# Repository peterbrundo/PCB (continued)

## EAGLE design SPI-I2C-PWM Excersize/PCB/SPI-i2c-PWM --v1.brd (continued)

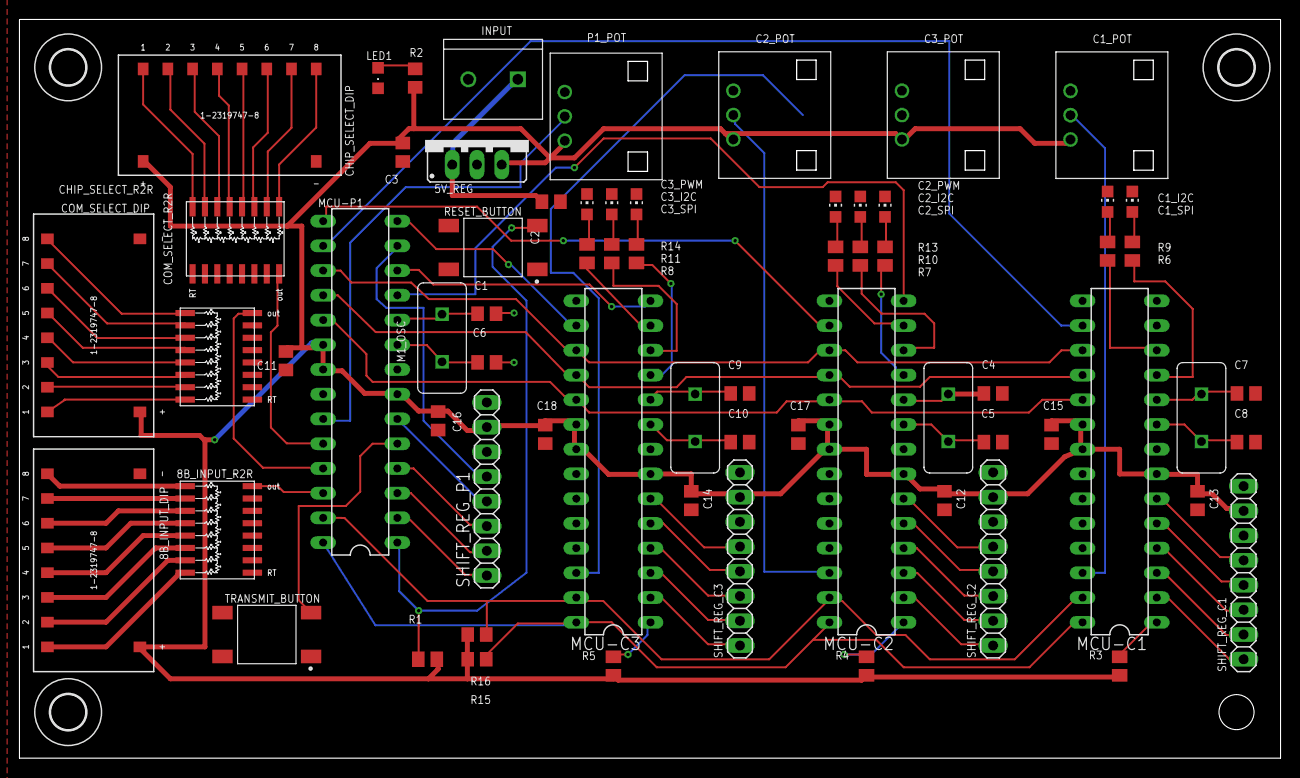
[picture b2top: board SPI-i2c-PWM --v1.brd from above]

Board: 2 copper layers, 129.4 x 75.7 mm, 72 parts (1 on the bottom side), 90 nets.

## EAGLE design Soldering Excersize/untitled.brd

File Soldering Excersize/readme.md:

# Soldering Practice
## Purpose
- First ever PCB (outside of work)
- Use spare parts on hand
  - Use NPN transistor
  - Use optoisolator
  - Voltage divider
- Different voltages +3.3V , +5V
- Surface mount soldering
  - 0805 Led & Resistor circuits
- Soldering practice

## Thoughts and reflections
- Good soldering practice
- Hard to re-use the board for other projects
  - next time include mounting holes
  - better breakouts for pin headers (hook up connections)
- [x] Never look back

*edit 11/29/2021*

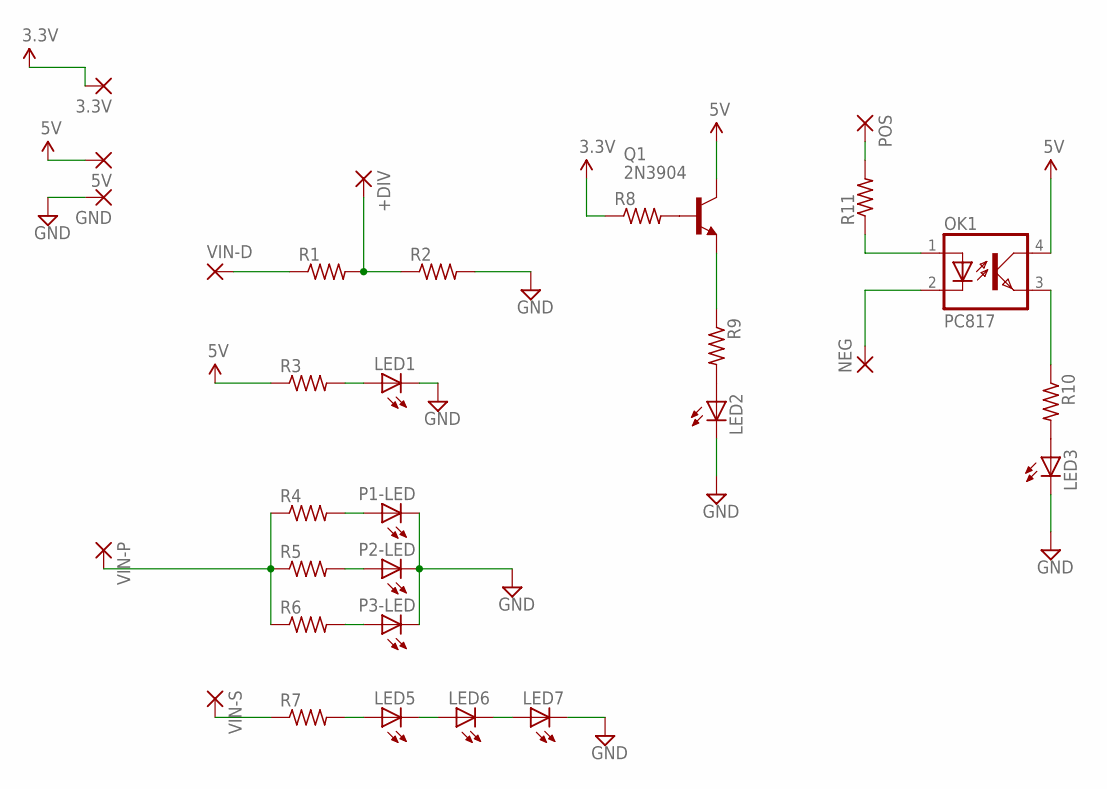
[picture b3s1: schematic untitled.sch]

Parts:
3.3V, 5V: 2,54/1,0
+DIV: 2,54/1,0
GND: 2,54/1,0
LED1, LED2, LED3, LED5, LED6, LED7: LEDCHIPLED_0805; CHIPLED_0805
NEG: 2,54/1,0
OK1: PC817; DIL04
P1-LED, P2-LED, P3-LED: LEDCHIPLED_0805; CHIPLED_0805
POS: 2,54/1,0
Q1: 2N3904; TO92
R1, R2, R3, R4, R5, R6, R7, R8, R9, R10, R11: R-US_R0805; R0805
VIN-D: 2,54/1,0
VIN-P: 2,54/1,0
VIN-S: 2,54/1,0

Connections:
3.3V: 3.3V.1, R8.1
5V: 5V.1, OK1.4 (COL), Q1.1 (C), R3.1
GND: GND.1, LED1.C, LED2.C, LED3.C, LED7.C, P1-LED.C, P2-LED.C, P3-LED.C, R2.2
unnamed: +DIV.1, R1.2, R2.1
unnamed: R1.1, VIN-D.1
unnamed: LED1.A, R3.2
unnamed: P1-LED.A, R4.2
unnamed: P2-LED.A, R5.2
unnamed: P3-LED.A, R6.2
unnamed: Q1.2 (B), R8.2
unnamed: LED5.C, LED6.A
unnamed: LED6.C, LED7.A
unnamed: LED5.A, R7.2
unnamed: R7.1, VIN-S.1
unnamed: R4.1, R5.1, R6.1, VIN-P.1
unnamed: LED2.A, R9.2
unnamed: Q1.3 (E), R9.1
unnamed: LED3.A, R10.2
unnamed: OK1.3 (EMIT), R10.1
unnamed: OK1.1 (A), R11.1
unnamed: POS.1, R11.2
unnamed: NEG.1, OK1.2 (C)

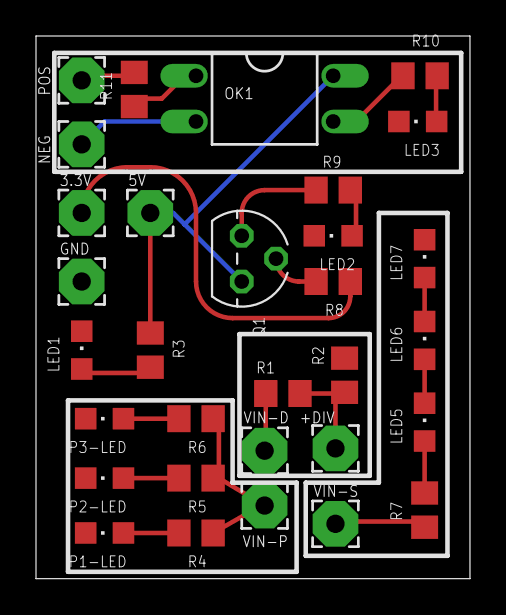
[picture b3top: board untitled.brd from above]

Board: 2 copper layers, 24.1 x 30.1 mm, 31 parts (0 on the bottom side), 22 nets.

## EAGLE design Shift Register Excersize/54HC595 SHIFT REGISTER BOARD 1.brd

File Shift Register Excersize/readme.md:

# Shift Register Exercise

Create a breakout for the SN74HC595 shift regsiter ([Texas instruments website and datasheet](https://www.ti.com/product/SN74HC595))

## Purpose

Develop a custom library for bit banging a shift register

## Goals

- Create custom library for bitbanging shift registers
  - Forwards and backwards (most significant bit and least significant bit)
  - Clear board
- Vertical mount thruhole resistors
- Use 2.54mm/0.1 inch pinheaders for breadboarding & reuseability
  -([See SPI-i2c Excercise](https://github.com/peterbrundo/PCB/tree/master/SPI-I2C-PWM%20Excersize)
- Use stencil, solder paste, and hot air to solder 0805 leds

## Thoughts and reflections
- The stencil turned out very large, so on recomendation I got myself some aviation metal cutting snips
- I used a metal putty knife to spread the solder which ended up sticking to the knife afterwards (big mistake)
- Easter eggs are from office space
- Consider daisy chaining these together
- Consider Max current draw per output pin

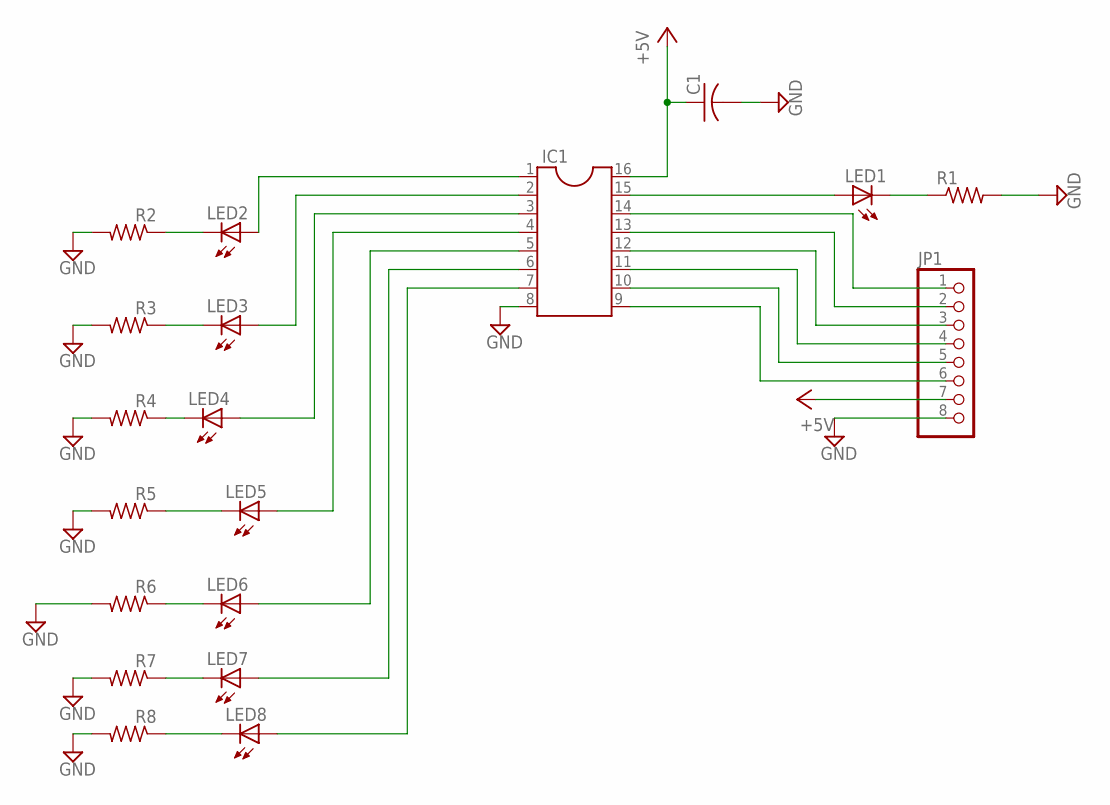
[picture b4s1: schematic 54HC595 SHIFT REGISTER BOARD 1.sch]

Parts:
C1: C-US050-025X075; C050-025X075
IC1: DIL16
JP1: PINHD-1X8; 1X08
LED1, LED2, LED3, LED4, LED5, LED6, LED7, LED8: LEDCHIPLED_0805; CHIPLED_0805
R1, R2, R3, R4, R5, R6, R7, R8: R-US_0309/V; 0309V

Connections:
+5V: C1.1, IC1.16, JP1.7
GND: C1.2, IC1.8, JP1.8, R1.2, R2.2, R3.2, R4.2, R5.2, R6.2, R7.2, R8.2
unnamed: IC1.15, LED1.A
unnamed: IC1.1, LED2.A
unnamed: IC1.2, LED3.A
unnamed: IC1.3, LED4.A
unnamed: IC1.4, LED5.A
unnamed: IC1.5, LED6.A
unnamed: IC1.6, LED7.A
unnamed: IC1.7, LED8.A
unnamed: LED8.C, R8.1
unnamed: LED7.C, R7.1
unnamed: LED6.C, R6.1
unnamed: LED5.C, R5.1
unnamed: LED4.C, R4.1
unnamed: LED3.C, R3.1
unnamed: LED2.C, R2.1
unnamed: IC1.14, JP1.1
unnamed: IC1.13, JP1.2
unnamed: IC1.12, JP1.3
unnamed: IC1.11, JP1.4
unnamed: IC1.10, JP1.5
unnamed: IC1.9, JP1.6
unnamed: LED1.C, R1.1

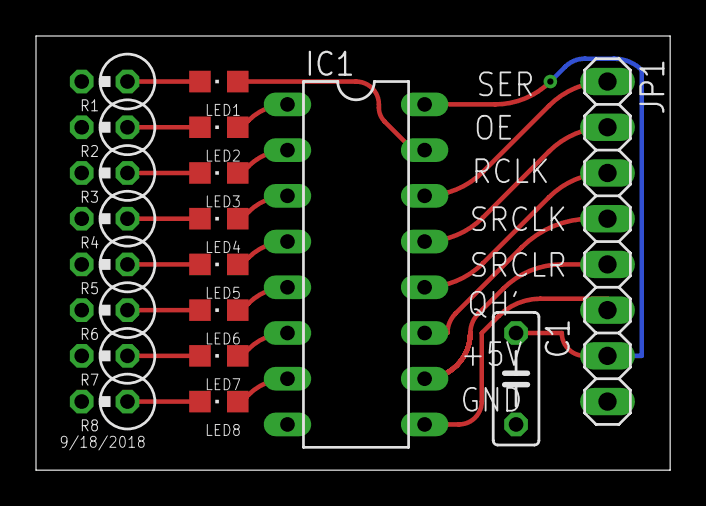
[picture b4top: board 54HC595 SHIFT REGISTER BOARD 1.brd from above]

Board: 2 copper layers, 35.2 x 24.1 mm, 19 parts (0 on the bottom side), 24 nets.

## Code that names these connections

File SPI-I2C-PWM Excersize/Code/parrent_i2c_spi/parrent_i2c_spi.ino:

//parent
#include <parent_bitbang_shift_register.h>
parent_bitbang_shift_register parent;

#define C3_LOW PORTB &= ~(CS3_PIN_MASK)
#define C3_HIGH PORTB |= (CS3_PIN_MASK)
#define C2_LOW PORTB &= ~(CS2_PIN_MASK)
#define C2_HIGH PORTB |= (CS2_PIN_MASK)
#define C1_LOW PORTB &= ~(CS1_PIN_MASK)
#define C1_HIGH PORTB |= (CS1_PIN_MASK)

//PORTB
       
#define CS3_PIN_MASK    0x01//PB0
#define CS2_PIN_MASK    0x02//PB1
#define CS1_PIN_MASK    0x04//PB2
#define POCI_MASK       0x08//PB3 
#define PICO_MASK       0x10//PB4 
#define SCK_MASK        0x20//PB5 
//xtal1                 0x40//PB6 
//xtal2                 0x80//PB7 
           
//PORTC

#define P1_POT1_MASK  0x01//PC0
#define CS_lDR_MASK   0x02//PC1
#define COM_lDR_MASK  0x04//PC2
#define BIT_LDR_MASK   0x08//PC3
#define SDA_MASK      0x10//PC4
#define SCL_MASK      0x20//PC5
//RESET               0x40//PC6
//N/A                 0x80//PC7

//PORTD

//P1 - SER           0x01//PD0
//P1 - OE            0x02//PD1
//P1 - RCLK          0x04//PD2
#define TX_BTN_MASK  0x08//PD3
//P1 - SRCLK         0x10//PD4
#define C2_OC0B_MASK 0x20//PD5
#define C3_OC0A_MASK 0x40//PD6
//P1 - SRCLR         0x80//PD7



int r2r_select = 0;
int currentbuttonstate = 0;
int prevbuttonstate = 1;
void setup() {


//CS pins as outputs, high by default
  DDRB |= (CS3_PIN_MASK | CS2_PIN_MASK | CS1_PIN_MASK);
  PORTB |= (CS3_PIN_MASK | CS2_PIN_MASK | CS1_PIN_MASK);  
/* Set POCI and SCK output*/

DDRB |= (POCI_MASK | SCK_MASK);
PORTB |= (POCI_MASK | SCK_MASK);

/* Enable SPI, set clock rate fck/16 */
SPCR = (1<<SPE)|(1<<MSTR)|(1<<SPR0);

//potentiometers and r2r ladders as inputs
  //DDRC &= ~(P1_POT1_MASK | CS_lDR_MASK | COM_lDR_MASK | BIT_LDR_MASK);

  //transmit butotn as input pullup
  DDRD &= ~(TX_BTN_MASK);
  PORTD |= (TX_BTN_MASK); 

 

  


      parent.parent_clearboard();
      parent.parent_shiftbyte(1);
      delay(1000);
      parent.parent_shiftbyte(2);
      delay(1000);
      parent.parent_shiftbyte(3);
      delay(1000);
      parent.parent_shiftbyte(4);
      delay(1000);
      parent.parent_clearboard();




}
void loop() {

  /*
  currentbuttonstate = digitalRead(3);
  if ( prevbuttonstate == 1 && currentbuttonstate == LOW  ) {
    r2r_select = r2r_select + 1;
    if (r2r_select > 2) {
      r2r_select = 0;
    }
  }
  prevbuttonstate = currentbuttonstate;
  delay(10);


  */
  /*
    switch (r2r_select) {
      case 0:
        parent.parent_clearboard();
        parent.parent_shiftbyte(map(analogRead(A0), 0, 1023, 0, 255));
        break;
      case 1:
        parent.parent_clearboard();
        parent.parent_shiftbyte(map(analogRead(A1), 0, 1023, 0, 255));
        break;
      case 2:
        parent.parent_clearboard();
        parent.parent_shiftbyte(map(analogRead(A2), 0, 1023, 0, 255));
        break;
      case 3:
        parent.parent_clearboard();
        parent.parent_shiftbyte(map(analogRead(A3), 0, 1023, 0, 255));
        break;
      default:
          break;
    }
  */
  
  parent_spi_cycle();
}


void parent_spi_cycle(){
  switch (r2r_select) {
    case 0:
      C1_LOW;
      parent_send_spi(0xAA);
      C1_HIGH;
      
      parent.parent_shiftbyte(1);
      delay(1000);
      
      C1_LOW;
      parent_send_spi(0);
      C1_HIGH;
      parent.parent_clearboard();
      delay(1000);
      break;
    case 1:
      C2_LOW;
      parent_send_spi(0xAA);
      C2_HIGH;
      
      parent.parent_shiftbyte(2);
      delay(1000);
      
      C2_LOW;
      parent_send_spi(0);
      C2_HIGH;
      parent.parent_clearboard();
      delay(1000);
      break;
    case 2:
      C3_LOW;
      parent_send_spi(0xAA);
      C3_HIGH;
      
      parent.parent_shiftbyte(3);
      delay(1000);
      
      C3_LOW;
      parent_send_spi(0);
      C3_HIGH;
      parent.parent_clearboard();
      delay(1000);
      break;
    default:
      break;
  }
  r2r_select = r2r_select+1;
  if (r2r_select > 2){
    r2r_select = 0;
  }
}
void parent_send_spi(byte info) {

/* Start transmission */
SPDR = char(info);
/* Wait for transmission complete */
while(!(SPSR & (1<<SPIF)))
;
}

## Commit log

2019-08-12 first commit yaya
2019-08-12 2nd commit yayyayayeeeee
2019-08-12 whaty Signed-off-by: Peter Brundage <peterbrundinator@gmail.com>
2019-08-12 whaty i'm not sure any more about this comiit messagse Signed-off-by: Peter Brundage <peterbrundinator@gmail.com>
2019-08-12 Create taa
2019-08-13 aa a
2019-08-13 new commit
2019-08-13 new commit delete
2019-08-13 First upload of real documents
2019-08-13 more commits
2019-08-13 Upload of code
2019-08-13 add visio drawing
2019-08-15 added test code for shift registers
2019-08-15 created new folders for everything
2019-08-15 fixed s1 librarry
2019-08-16 lol some stuff happen idk k lmao xD
2019-08-19 Added some more stuff
2019-08-20 Fixed shift register for the master Displayed 0-255 and 255-0 both for loop and potentiometer controlled Shown feedback on R2R ladders Gotta adjust Map function to 1023 and NOT 1024
    **Currently working on PCB for buisness card, SPI and I2C functionality after next project parts have been ordered
2021-06-08 new readme
    same as the one on the main page
2021-06-19 Create Buisness Card Project
2021-06-19 uploaded my buisness card project
    please be all in on folder... I don't have github on this second computer!
2021-06-19 added .stp file and put the board renders at the top
2021-06-19 got rid of some old renders, moved to the top
2021-06-19 added gerber files and partlist
2021-10-21 Create Test
2021-11-09 modified test file
2021-11-09 Run test on Test file
2021-11-09 removed change on test file
2021-11-10 changed wording
2021-11-10 changed wording, need to work on keeping things organized
2021-11-10 updated shift_register library - removed redundant r-clock pulses
2021-11-10 Simplified shift register library, removed unsued functions, updated arduino demo file
2021-11-10 Changed shift_register library to bitbang_shift_register, updated arduino example
2021-11-10 code format changes, removed a comment
2021-11-15 Created .gitignore to handle weird eagle files
    from ->https://github.com/github/gitignore/blob/master/Eagle.gitignore
2021-11-16 added captouch folder for implementing cap touch on buisness card
2021-11-16 Added a readme and high level concept drawing for SPI-I2C Excercise
2021-11-16 updated readme for project goals
2021-11-17 updates to i2c-spi scheamtic and board files plus new output images
2021-11-17 forgot to save .brd file before last commit
2021-11-18 included functionality for python script
    added instructions for baud rate settings
    added instructions for commenting out certain serial.print() lines
    **this can be made better**
2021-11-18 Added Python based GUI
2021-11-23 added new child and parent SPI capability, removed old files
2021-11-23 parent now outputs led number of which child it's talking to
2021-11-24 included direct port i/o manipulation and led pin registers
2021-11-24 added direct port manipulation for parent
2021-11-24 changed parrent_i2c_spi.ino to parent_i2c_spi.ino
2021-11-24 removed extra folder + old child.ino
2021-11-29 update readme - added formats
2021-11-29 Rename readme.txt to readme.md
2021-11-29 Update formatting for readme
    removed some ' " marks in the project title
2021-11-29 Update readme
    added bullet points (unordered list)
2021-11-29 Update readme (formating)
    spaces for # headers
    included some
2021-11-29 Update readme (lists)
    Fix nested lists
2021-11-29 Update readme
    Fix another nested list
2021-11-29 Update Readme
    Last update I promise
    removed a (
2021-11-29 Cleaning up Business Card readme
    Readme.txt -> Readme.md
    Github formatting
    cleaned up wording
    Added more credit to the obdev folks
    added some next steps (cap touch!)
2021-11-29 Update readme
    added italicized update day/month/year
2021-11-29 Created readme.md
2021-11-30 Added images of working bitbang shift register
    images of wiring between arduino and shift register board
    -more images to follow shortly
2021-11-30 Deleted a test file
2021-12-09 added new step file, f3d file, new renders, new folder for renders and pictures
2021-12-09 Create BOMChecker.bat
    messy way of checking part status
2021-12-09 Create EagleFilePuller.bat
    Made this batch file to pull files from different directories into my local github repository.
    Probably going to be most used with Eagle files
    Need to ad
2021-12-09 Added AtmelStudio application files
    This version should make the business card behave as a regular number pad
2021-12-10 added numpad support
2021-12-11 added lumissil IS31SE5111 touch sensor parts TSSOP-16 and TSSOP24 ECAD models to library
2021-12-11 updates to capacitor and crystal symbols, added a bat file to pull the library file
2021-12-11 created eagle board and eagle schematic files for REV 2.0, created .batch file puller helper
